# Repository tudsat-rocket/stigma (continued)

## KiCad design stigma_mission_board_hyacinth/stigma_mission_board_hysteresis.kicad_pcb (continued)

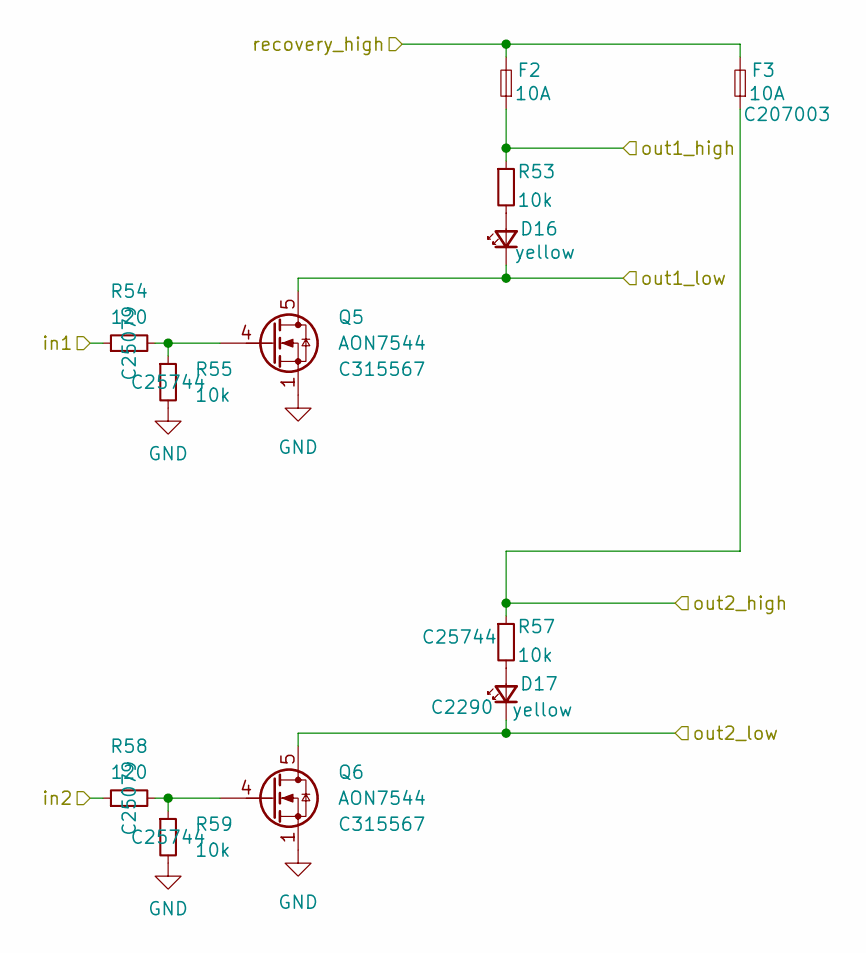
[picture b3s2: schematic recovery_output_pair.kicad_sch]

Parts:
D16, D17: yellow; LED_0603_1608Metric; LCSC C2290
F2, F3: 10A; Fuse_1206_3216Metric; LCSC C207003
Q5, Q6: AON7544; DFN-8-1EP_3x3mm_P0.65mm_EP1.55x2.4mm; LCSC C315567
R53, R55, R57, R59: 10k; R_0402_1005Metric; LCSC C25744
R54, R58: 120; R_0402_1005Metric; LCSC C25079

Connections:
/Recovery Output Pair 1/recovery_high: F2.2, F3.2; also elsewhere on the board
GND: Q5.1 (S), Q5.2 (S), Q5.3 (S), Q6.1 (S), Q6.2 (S), Q6.3 (S), R55.2, R59.2; also elsewhere on the board
unnamed: D16.2 (A), R53.2
unnamed: D17.2 (A), R57.2
unnamed: Q5.4 (G), R54.2, R55.1
unnamed: Q6.4 (G), R58.2, R59.1
R1_H: F2.1, R53.1; also elsewhere on the board
R1_L: D16.1 (K), Q5.5 (D), Q5.6 (D), Q5.7 (D), Q5.8 (D), Q5.9 (D); also elsewhere on the board
R2_H: F3.1, R57.1; also elsewhere on the board
R2_L: D17.1 (K), Q6.5 (D), Q6.6 (D), Q6.7 (D), Q6.8 (D), Q6.9 (D); also elsewhere on the board
RECOVERY1: R54.1; also elsewhere on the board
RECOVERY2: R58.1; also elsewhere on the board

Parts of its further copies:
F4, F5: 10A; Fuse_1206_3216Metric; LCSC C207003
Q7, Q8: AON7544; DFN-8-1EP_3x3mm_P0.65mm_EP1.55x2.4mm; LCSC C315567
R60, R62, R64, R66: 10k; R_0402_1005Metric; LCSC C25744
R61, R65: 120; R_0402_1005Metric; LCSC C25079

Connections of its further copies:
/Recovery Output Pair 1/recovery_high: F4.2, F5.2; also elsewhere on the board
GND: Q7.1 (S), Q7.2 (S), Q7.3 (S), Q8.1 (S), Q8.2 (S), Q8.3 (S), R62.2, R66.2; also elsewhere on the board
unnamed 60: R60.2; also elsewhere on the board
unnamed 61: R64.2; also elsewhere on the board
unnamed: Q7.4 (G), R61.2, R62.1
unnamed: Q8.4 (G), R65.2, R66.1
R3_H: F4.1, R60.1; also elsewhere on the board
R3_L: Q7.5 (D), Q7.6 (D), Q7.7 (D), Q7.8 (D), Q7.9 (D); also elsewhere on the board
R4_H: F5.1, R64.1; also elsewhere on the board
R4_L: Q8.5 (D), Q8.6 (D), Q8.7 (D), Q8.8 (D), Q8.9 (D); also elsewhere on the board
RECOVERY3: R61.1; also elsewhere on the board
RECOVERY4: R65.1; also elsewhere on the board

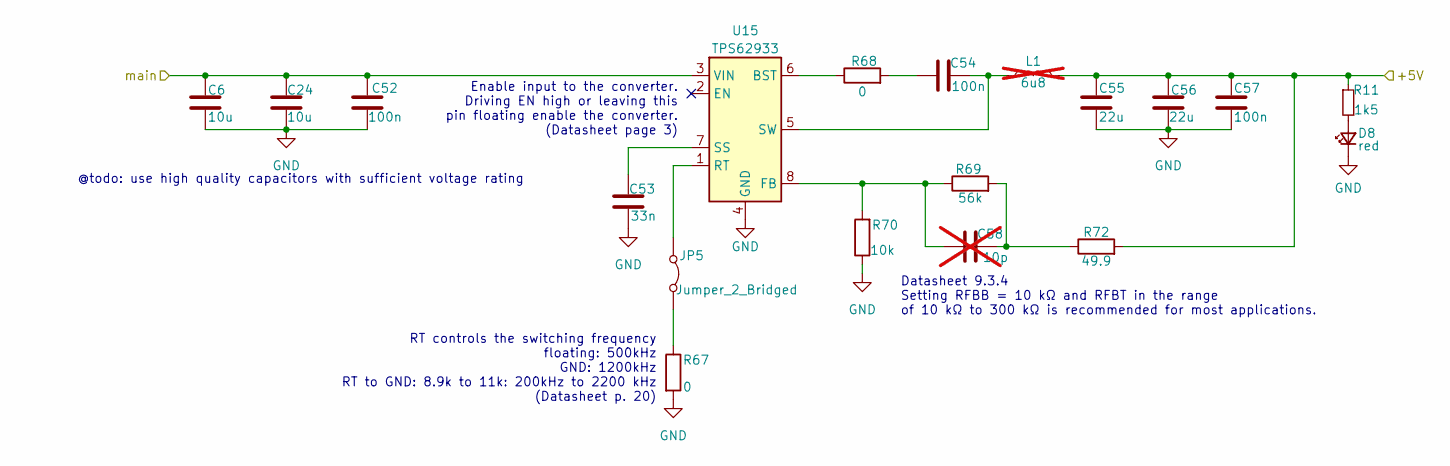
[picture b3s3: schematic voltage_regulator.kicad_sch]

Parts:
C6, C24: 10u; C_0603_1608Metric; LCSC# C96446
C52: 100n; C_0402_1005Metric; LCSC# C1525
C53: 33n; C_0402_1005Metric; LCSC C7419416
C54: 100n; C_0402_1005Metric
C55, C56: 22u; C_0603_1608Metric; LCSC C45783
C57: 100n; C_0402_1005Metric; LCSC C1525
C58: 10p; C_0603_1608Metric; not fitted
D8: red; LED_0603_1608Metric; LCSC C2286
JP5: Jumper_2_Bridged; SolderJumper-2_P1.3mm_Bridged_Pad1.0x1.5mm
L1: 6u8; L_Wuerth_XHMI-6060; not fitted
R11: 1k5; R_0402_1005Metric; Part# ESR03EZPJ221; LCSC C25867
R67: 0; R_0603_1608Metric; LCSC# C21189
R68: 0; R_0402_1005Metric; LCSC # C106231
R69: 56k; R_0603_1608Metric; LCSC# C23206
R70: 10k; R_0603_1608Metric; LCSC# C25804
R72: 49.9; R_0603_1608Metric
U15: TPS62933; SOT-583-8

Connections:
+5V: C55.1, C56.1, C57.1, L1.2, R11.1, R72.2; also elsewhere on the board
GND: C6.2, C24.2, C52.2, C53.2, C55.2, C56.2, C57.2, D8.1 (K), R67.2, R70.1, U15.4 (GND); also elsewhere on the board
unnamed: C54.2, R68.2
unnamed: C58.1, R69.2, R72.1
unnamed: D8.2 (A), R11.2
unnamed: JP5.1 (A), U15.1 (RT)
unnamed: JP5.2 (B), R67.1
unnamed: R68.1, U15.6 (BST)
unnamed: C58.2, R69.1, R70.2, U15.8 (FB)
unnamed: C53.1, U15.7 (SS)
unnamed: C54.1, L1.1, U15.5 (SW)
main: C6.1, C24.1, C52.1, U15.3 (VIN); also elsewhere on the board

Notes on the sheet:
Enable input to the converter. Driving EN high or leaving this pin floating enable the converter. (Datasheet page 3)
RT controls the switching frequency floating: 500kHz GND: 1200kHz RT to GND: 8.9k to 11k: 200kHz to 2200 kHz (Datasheet p. 20)
@todo: use high quality capacitors with sufficient voltage rating
Datasheet 9.3.4 Setting RFBB = 10 kΩ and RFBT in the range of 10 kΩ to 300 kΩ is recommended for most applications.

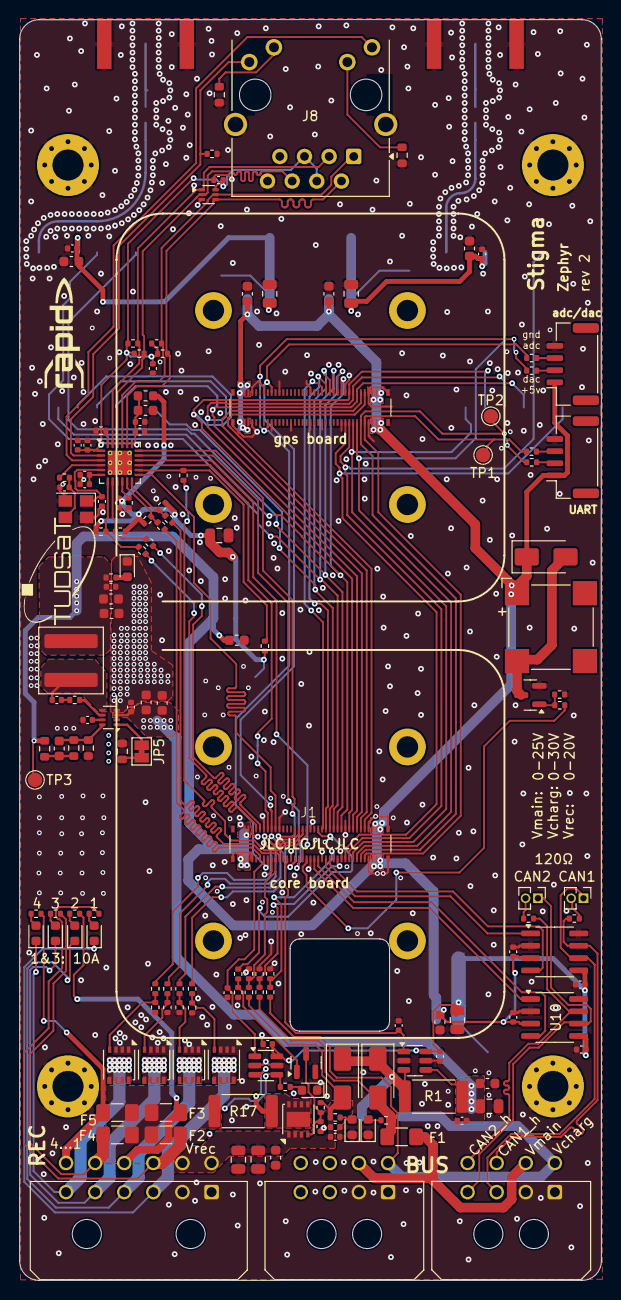
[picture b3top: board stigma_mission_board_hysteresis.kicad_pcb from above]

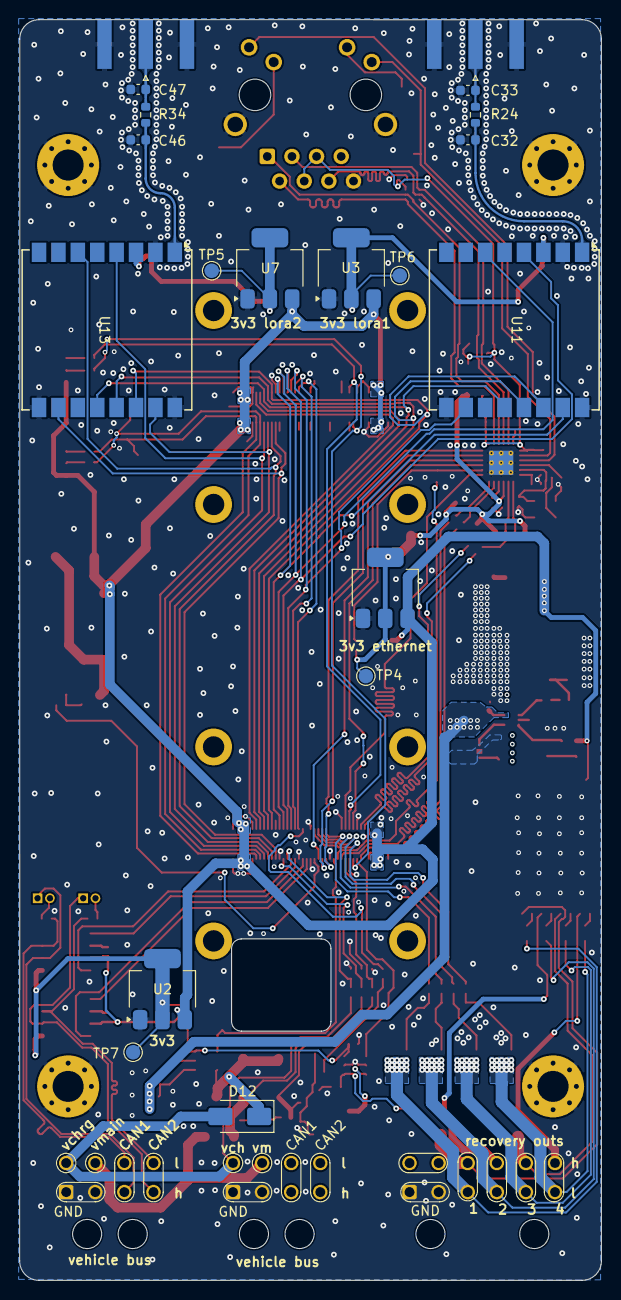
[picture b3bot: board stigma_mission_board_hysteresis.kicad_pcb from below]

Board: 4 copper layers, 60.0 x 130.0 mm, 181 parts (19 on the bottom side), 124 nets.

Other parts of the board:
D18, D19: white; LED_0603_1608Metric

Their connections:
unnamed 60: D18.2 (A); also elsewhere on the board
unnamed 61: D19.2 (A); also elsewhere on the board
R3_L: D18.1 (K); also elsewhere on the board
R4_L: D19.1 (K); also elsewhere on the board

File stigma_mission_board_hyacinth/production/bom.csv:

Designator,Footprint,Quantity,Value,LCSC Part #
BZ1,MagneticBuzzer_CUI_CMT-8504-100-SMT,1,Buzzer,C781886
"C10, C16, C18, C22, C23, C3, C8",0805,7,22u,C45783
"C11, C14, C25, C26, C27, C28, C29, C30, C35, C36, C37, C38, C39, C40, C44, C45, C49, C57",0402,18,100n,C1525
"C15, C17, C21, C34, C4, C43, C48, C7, C9",0603,9,10u,C96446
"C19, C20, C41, C5",0402,4,1u,C52923
"C24, C6",0603,2,10u,
C42,0402,1,470p,C1537
"C50, C51",0402,2,10p,C32949
"C52, C54",0402,2,100n,
C53,0402,1,33n,C7419416
"C55, C56",0603,2,22u,C45783
"D10, D16, D17, D18, D19",0603,5,white,C2290
"D15, D2, D3",D_SMA,3,SS34,C8678
"D5, D6, D8",0603,3,red,C2286
F1,1206,1,3A,C99558
"F2, F3, F4, F5",1206,4,10A,C207003
FB1,0603,1,FerriteBead,C1002
"J1, J2",core-board-inner-mounting-holes,2,DF40C-70DS-0.4V(51),C294854
"J10, J9",JST_GH_SM04B-GHS-TB_1x04-1MP_P1.25mm_Horizontal,2,JST-GH,C189895
"J3, J4",Molex_Micro-Fit_3.0_43045-0800_2x04_P3.00mm_Horizontal,2,~,
J5,Molex_Micro-Fit_3.0_43045-1200_2x06_P3.00mm_Horizontal,1,~,
"J6, J7",SMA_Amphenol_132289_EdgeMount,2,SMA,
J8,RJ45_Wuerth_7499010211A_Horizontal,1,RJ45_Wuerth_7499010211A,
"JP3, JP4",PinHeader_1x02_P1.27mm_Vertical,2,Jumper_2_Small_Open,
JP5,SolderJumper-2_P1.3mm_Bridged_Pad1.0x1.5mm,1,Jumper_2_Bridged,
L1,L_Wuerth_XHMI-6060,1,6u8,
Q1,DFN-8-1EP_3x3mm_P0.65mm_EP1.55x2.4mm,1,AON7423,C99711
"Q2, Q4",SOT-23,2,AO3400A,C20917
"Q5, Q6, Q7, Q8",DFN-8-1EP_3x3mm_P0.65mm_EP1.55x2.4mm,4,AON7544,C315567
"R1, R17",2512,2,"5m, 1%",C723630
"R10, R12, R15, R19, R25, R27, R28, R29, R37, R46, R48, R53, R55, R57, R59, R6, R60, R62, R64, R66, R7, R8, R9",0402,23,10k,C25744
"R11, R26",0402,2,1k5,C25867
"R13, R14, R22, R44, R54, R58, R61, R65",0402,8,120,C25079
"R2, R3, R4, R56",0402,4,100k,C25741
"R24, R34, R67",0603,3,0,
"R30, R31, R32, R33",0402,4,51,C25125
"R35, R36, R38, R41, R42, R43, R51, R52",0402,8,33,C25161
"R39, R50",0402,2,0,C17168
R40,0402,1,12.1k,C25752
"R45, R47",0603,2,270,C22966
R68,0402,1,0,
R69,0603,1,56k,
R70,0603,1,10k,
R72,0603,1,49.9,
"TP1, TP2, TP3, TP4, TP5, TP6, TP7",TestPoint_Pad_D1.5mm,7,TestPoint,
"U10, U8",SOIC-8_3.9x4.9mm_P1.27mm,2,MCP2562FD,C124016
"U11, U13",Ai-Thinker-Ra-01-LoRa,2,Ai-Thinker-Ra-01,
U12,SOT-563,1,TPD4E1U06,C527516
U14,VQFN-24-1EP_4x4mm_P0.5mm_EP2.5x2.5mm_ThermalVias,1,LAN8742A,C621424
U15,SOT-583-8,1,TPS62933,
"U2, U3, U6, U7",SOT-223-3_TabPin2,4,AZ1117I-3.3,C92102
U4,SOT-23-6,1,INA181A3,C2652255
U9,SOT-23-6,1,INA181A2,C2058784
Y1,Crystal_SMD_3225-4Pin_3.2x2.5mm,1,25MHz,C9006

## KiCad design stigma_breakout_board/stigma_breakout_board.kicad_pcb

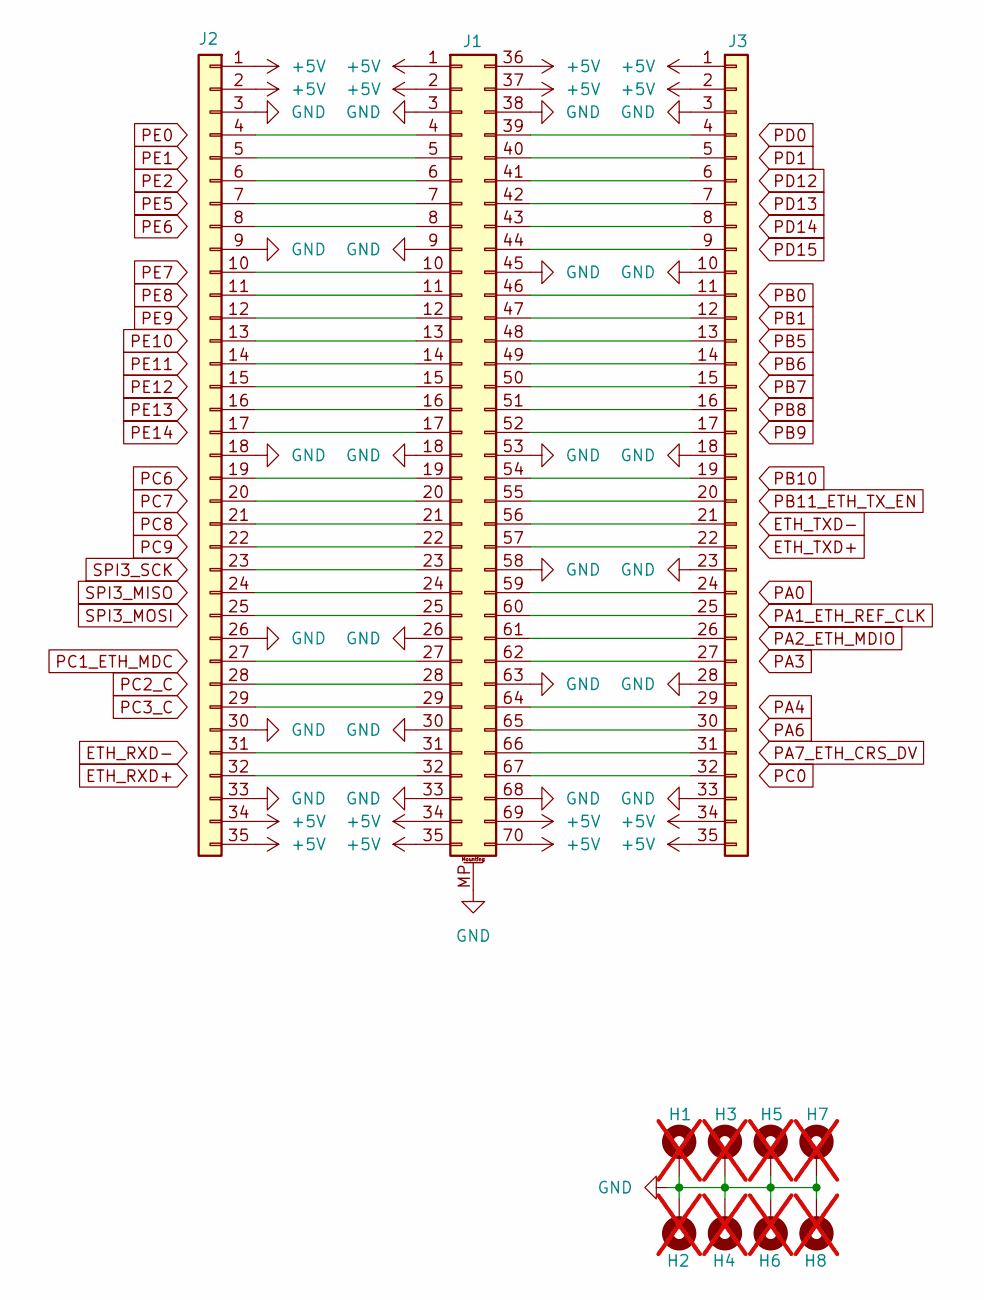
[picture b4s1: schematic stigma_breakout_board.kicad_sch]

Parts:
H1, H3, H5, H7: MountingHole_Pad; MountingHole_4.3mm_M4_ISO14580_Pad; not fitted
H2, H4, H6, H8: MountingHole_Pad; MountingHole_2.2mm_M2_ISO14580_Pad; not fitted
J1: DF40C-70DS-0.4V-receptacle
J2, J3: Conn_01x35; PinHeader_1x35_P2.54mm_Vertical

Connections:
+5V: J1.1, J1.2, J1.34, J1.35, J1.36, J1.37, J1.69, J1.70, J2.1, J2.2, J2.34, J2.35, J3.1, J3.2, J3.34, J3.35
GND: H1.1, H2.1, H3.1, H4.1, H5.1, H6.1, H7.1, H8.1, J1.3, J1.9, J1.18, J1.26, J1.30, J1.33, J1.38, J1.45, J1.53, J1.58, J1.63, J1.68, J1.MP (MountPin), J2.3, J2.9, J2.18, J2.26, J2.30, J2.33, J3.3, J3.10, J3.18, J3.23, J3.28, J3.33
unnamed: J1.4, J2.4
unnamed: J1.5, J2.5
unnamed: J1.6, J2.6
unnamed: J1.7, J2.7
unnamed: J1.8, J2.8
unnamed: J1.10, J2.10
unnamed: J1.11, J2.11
unnamed: J1.12, J2.12
unnamed: J1.13, J2.13
unnamed: J1.14, J2.14
unnamed: J1.15, J2.15
unnamed: J1.16, J2.16
unnamed: J1.17, J2.17
unnamed: J1.19, J2.19
unnamed: J1.20, J2.20
unnamed: J1.21, J2.21
unnamed: J1.22, J2.22
unnamed: J1.23, J2.23
unnamed: J1.24, J2.24
unnamed: J1.25, J2.25
unnamed: J1.27, J2.27
unnamed: J1.28, J2.28
unnamed: J1.29, J2.29
unnamed: J1.31, J2.31
unnamed: J1.32, J2.32
unnamed: J1.39, J3.4
unnamed: J1.40, J3.5
unnamed: J1.41, J3.6
unnamed: J1.42, J3.7
unnamed: J1.43, J3.8
unnamed: J1.44, J3.9
unnamed: J1.46, J3.11
unnamed: J1.47, J3.12
unnamed: J1.48, J3.13
unnamed: J1.49, J3.14
unnamed: J1.50, J3.15
unnamed: J1.51, J3.16
unnamed: J1.52, J3.17
unnamed: J1.54, J3.19
unnamed: J1.55, J3.20
unnamed: J1.56, J3.21
unnamed: J1.57, J3.22
unnamed: J1.59, J3.24
unnamed: J1.60, J3.25
unnamed: J1.61, J3.26
unnamed: J1.62, J3.27
unnamed: J1.64, J3.29
unnamed: J1.65, J3.30
unnamed: J1.66, J3.31
unnamed: J1.67, J3.32

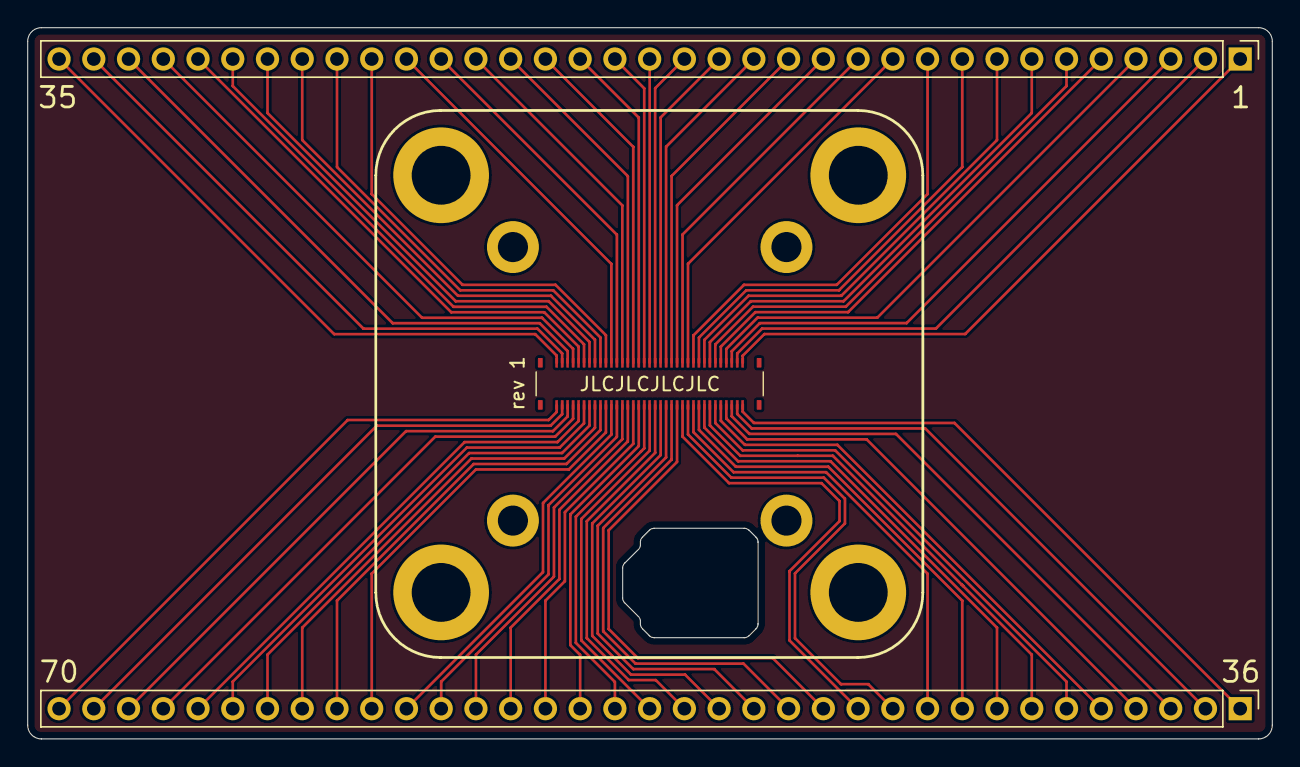
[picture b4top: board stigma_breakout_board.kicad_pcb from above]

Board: 2 copper layers, 91.0 x 52.0 mm, 11 parts (0 on the bottom side), 52 nets.

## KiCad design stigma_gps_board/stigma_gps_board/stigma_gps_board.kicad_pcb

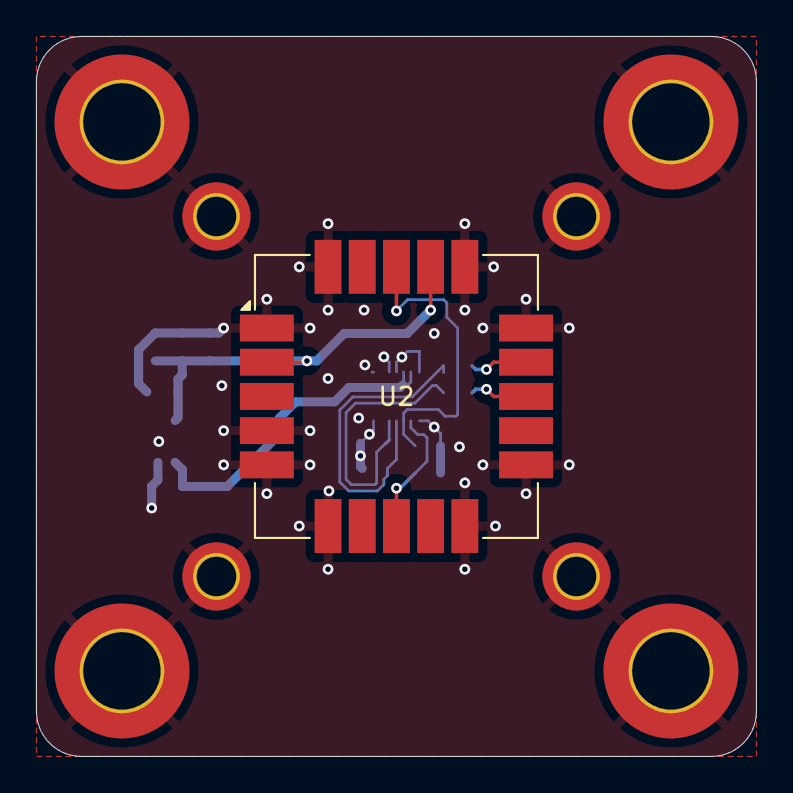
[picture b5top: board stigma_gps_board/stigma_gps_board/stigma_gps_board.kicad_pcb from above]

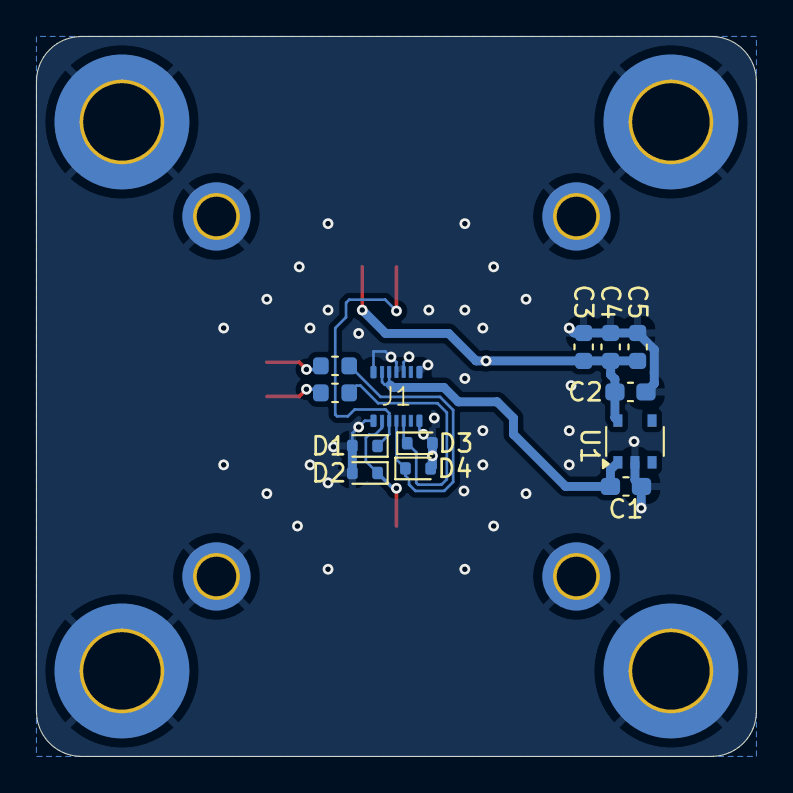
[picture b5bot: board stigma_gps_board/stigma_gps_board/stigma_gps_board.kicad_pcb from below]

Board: 2 copper layers, 40.0 x 40.0 mm, 22 parts (13 on the bottom side), 9 nets.

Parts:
C1, C2: 1uF; C_0603_1608Metric_Pad1.08x0.95mm_HandSolder
C3, C4, C5: 100n; C_0603_1608Metric
D1, D2, D3, D4: ESD5Zxx; D_SOD-523
H1, H2, H3, H4: MountingHole_Pad; MountingHole_2.2mm_M2_DIN965_Pad_TopBottom
H5, H6, H7, H8: MountingHole_Pad; MountingHole_4.3mm_M4_DIN965_Pad_TopBottom
J1: Conn_02x05_Top_Bottom; DF40GB-10DP-0.4V-plug
L1, L2: BEAD; L_0603_1608Metric
U1: NCP115AMX120TCG; TSOP-5_1.65x3.05mm_P0.95mm
U2: SAM-M10Q; ublox_SAM-M8Q_HandSolder

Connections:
5V: C1.2, J1.1, J1.2, U1.1 (IN)
+3.3V: C2.2, C3.2, C4.2, C5.2, U1.5 (OUT), U2.2 (VCC_IO), U2.17 (VCC)
GND: C1.1, C2.1, C3.1, C4.1, C5.1, D1.2 (A), D2.2 (A), D3.2 (A), D4.2 (A), H1.1, H2.1, H3.1, H4.1, H5.1, H6.1, H7.1, H8.1, J1.3, J1.4, J1.s (shield), U1.2 (GND), U2.1 (GND), U2.4 (GND), U2.5 (GND), U2.6 (GND), U2.10 (GND), U2.11 (GND), U2.15 (GND), U2.16 (GND), U2.20 (GND)
GPS_RESET: D1.1 (K), J1.7, U2.18 (~RESET)
GPS_SAFEBOOT: D2.1 (K), J1.6, U2.8 (~SAFEBOOT)
unnamed: L1.1, U2.14 (RXD)
unnamed: L2.1, U2.13 (TXD)
UART2_RX: D3.1 (K), J1.9, L2.2
UART2_TX: D4.1 (K), J1.8, L1.2

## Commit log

2024-12-16 add first components
2024-12-16 add readme
2024-12-16 initialized gps board with first parts and infos in the scematic
2024-12-19 added esd protection, finished scematic
2024-12-20 Clean up previous pinout attempt
2024-12-20 first revision of gps board finished
2024-12-20 added stm32 and connector pinout
2024-12-26 Add TPD4E001 TVS component
2024-12-26 Flesh out 70-pin DF40 plug footprint
2024-12-26 First pass of signal routing
2024-12-29 Route power, please DRC
2024-12-29 Rename LCSC part no. property
2024-12-29 Update LCSC references
2024-12-30 Tweak routing
2024-12-30 Minor layout tweaks
2024-12-30 Minor routing tweaks, add net colors
2025-01-05 minor changes
2025-01-05 Add correct load capacitors, tweak USB routing, fab options
2025-01-06 Add first draft of breakout board
2025-01-13 add connector and fix recovery
2025-01-22 last minute changes
2025-01-22 Move GPS project to root folder
2025-01-24 add more components
2025-01-27 added second lora module, adapted connector pins
2025-01-27 add file
2025-01-27 rename recovery_output file
2025-01-29 fix ethernet, add VH bus, fix voltage sensing
2025-01-30 improve pinout and add more descriptions
2025-02-01 fixed a few small issues, added some part numbers and footprints
2025-02-01 changed mosfet to more suitable one
2025-02-01 changed vehicle bus connector numbering
2025-02-04 add high_voltage to pwm signal again
2025-02-06 added 3.3V redundant circuit and recovery output simulation
2025-02-06 deleted autosave
2025-02-06 simplified cont check
2025-02-07 some changes to the recovery outputs
2025-02-09 uploaded files to share current not working parts
2025-02-11 Added missing footprints and changed GPS Connector
2025-02-11 Added missing Footprints and changed GPS Connector
    into the right directory this time
2025-02-11 fixed some errors
2025-02-16 add RJ45 sym
2025-02-16 add rj45 connector
2025-02-24 changed pcb layout and added first tracks
2025-02-26 placed recovery outputs and vehicle bus, fixed errors in schematic
2025-02-28 made board more compact, started routing recovery outputs
2025-02-28 some tydiing up and adding footprints
2025-02-28 added the other 2 recovery outputs and sorted all components
2025-03-02 Add lock files to gitignore
2025-03-02 Restore stigma_core_board from 4524638
2025-03-02 Add footprint representing core board for mission boards
2025-03-03 added gps footprint
2025-03-03 added GPS and Coreboard connector, changed ROs
2025-03-03 added a few footprints for the missionboard
2025-03-21 added 3d models of connectors
2025-03-21 rearanged some stuff
2025-03-24 fixed footprint
2025-03-24 changed pcb design. currently not working
2025-03-24 Layed out 3.3v regulators, buzzer, shift register and current + voltage sensing on the mission board pcb
2025-03-25 changed capacitors
2025-03-26 added 5v regulators to pcb
2025-03-29 added ethernet layout to pcb and changed minor errors
2025-04-03 Temp save of changes. Changed PCB size, layout and number of Connectors
2025-04-03 Added more components to NEW pcb layout.
2025-04-04 changed outer layout
2025-04-06 added some 3d models
2025-04-07 added 3d models and datasheets
2025-04-18 Rework recovery outputs to 2x2 low side
2025-04-19 Refactor schematic, esp. recovery outputs, prepare for final layout
2025-04-21 start routing
2025-04-22 progress on routing, add some 3d models
2025-04-27 progress on mission board layout
2025-05-09 Complete routing of mission board
2025-05-12 Last minute changes to mission board
2025-06-15 Update GPS board for mission board
2025-06-16 Add LCSC part number to Reg
2025-06-16 Forgot to add in schematic
2025-10-17 remove rst and boot from USB TSV diode
2025-10-18 add pinout file
2025-11-09 replace voltage regulator and increase edge-cut corner radius to match the core board
2025-12-01 fix voltage regulator
2025-12-01 increase ref to 2
2025-12-14 finish routing, flyback is still wip
2026-01-10 core: Handle DRC warnings
2026-01-10 core: Replace flash w/ W25Q256, WSON 8x6
2026-01-10 core: Connect VREF to VDDA
2026-01-10 core: Final bom changes, production files
2026-01-24 final adjustments for mission board rev2
2026-01-25 add voltage regulator schematics
2026-01-26 added some comments
2026-02-16 improve can traces at VB, use smaller resistor for voltage reg.
2026-03-09 remove cont check and rec jumper
2026-03-23 design check finished, some cosmetic changes, part adaptions, prints, etc.
2026-04-29 finished req. checklist, marginal changes
2026-04-29 added production files
2026-05-01 some lcsc number changes
2026-05-04 some last changes before ordering
2026-05-04 added schematic as pdf
